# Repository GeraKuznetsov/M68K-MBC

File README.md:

A M68k Multi-Board Computer design. The design basics is as follows:
1) A backplane PCB contains the majority of the bus, such as the address and data lines.
2) Cards slot into the backplane. Cards other then the CPU card should have bus buffers to lower the bus load. (I might give the CPU card buffers too).
3) The 68k's 16MB memory map is split into 16 1MB regions. This is because the two memory chips used, the sst39f040 flash and AS6C4008 ram are both 0.5MB. (So when you put two of them together to get 16 bits, you end up with 1MB per bank).
4) Address decoding is done by a pair of decoders on the CPU card. The CS lines from a header on the side of the CPU card to headers on the sides of the other cards, ideally with a twisted ground for each CS line. In the future these lines could be moved into the backplane. 
5) If the card is less then 10x10 cm, I make it 4-layer. 4-layer boards bigger then 10x10cm are too expensive. 
6) the connectors are DIN41612
7) Line the 16 CS lines, the 7 interrupt lines are also jumpers you plug into the side of the board. There are also 8 interrupt enable jumpers that need to go from the IO card to the CPU card if you want to use one of the parallel output ports as an interrupt enable status port. 

IO and CPU cards are currently completely untested, and the memory card is missing a chip to enable the card's data transmitters. 

/Schematic/:
The actual MBC schematics
Note: LS components are sometimes used when the library has no corresponding HC part. All parts are meant to be HC, with the exception of LVC in 5v->3v translation (output to SD card) and HCT in 3v->5v translation (input from SD card). You can use ACT (or AC if you are feeling brave) but at <16Mhz there should not be a need for fast ACT/AC buffers/gluelogic, especially due to the 68k's slow bus cycles (in comparison to say a 6502 or a z80).

Schematics/BP - design for the backplane (TESTED)
Schematics/CPU - design for CPU card. (NOT TESTED)
Schematics/IO - design for IO card with SD card, PIO, PS2, RTC. (NOT TESTED)
Schematics/MEMv2 - second version of the memory card, doesn't even have the layout done. (NOT FINISHED)
Schematics/MEMv1 - first version of the memory card, missing 74HC20 and gate to enable the card bus buffers (TESTED)
Schematics/Footpp - various footprints
Schematics/Lib - various symbols

/Code/
WIP code, just testing stuff, will eventually be OS

/sst39f040_inBB/:
Allows you to connect an arduino mega to the backplane and program the flash chips on the memory card in-circuit. 
TODO: document this better
sst39f040_inBB/avr - the arduino mega code
sst39f040_inBB/send.py - script file to send the data, requires serial lib

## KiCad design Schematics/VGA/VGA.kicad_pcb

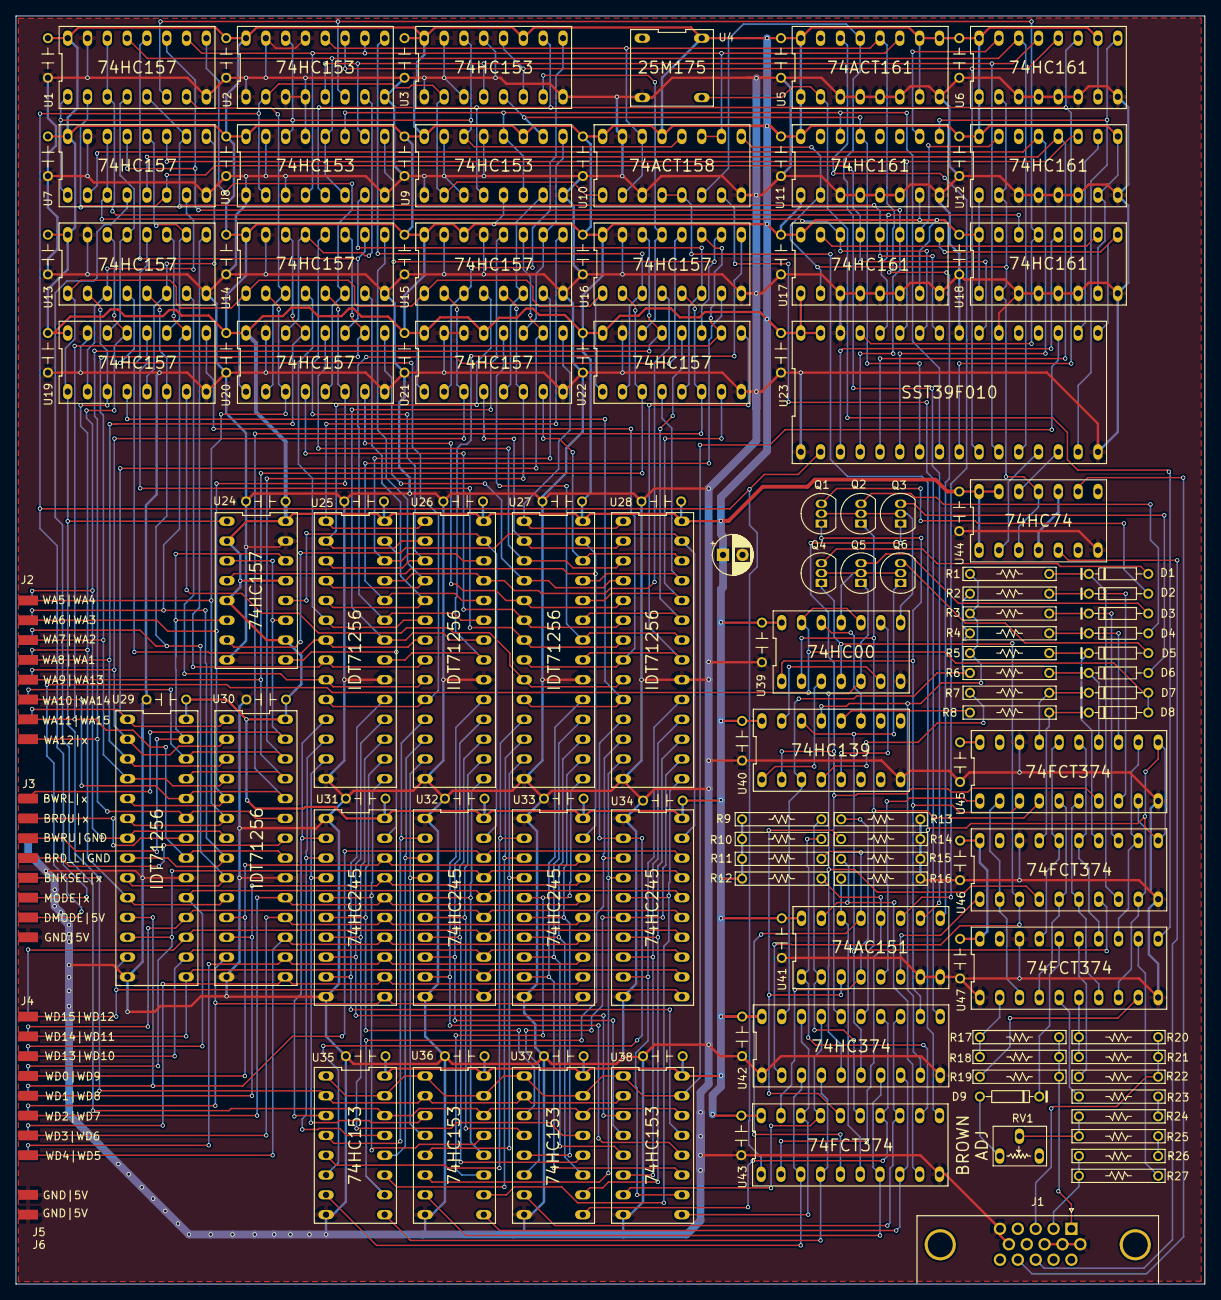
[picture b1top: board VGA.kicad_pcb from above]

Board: 2 copper layers, 152.4 x 162.6 mm, 143 parts (0 on the bottom side), 229 nets.

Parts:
C1, C2, C3, C4, C5, C6, C7, C8, C9, C10, C11, C12, C13, C14, C15, C16, C17, C18, C19, C20, C21, C22, C23, C24, C25, C26, C27, C28, C29, C30, C31, C32, C33, C34, C35, C36, C37, C38, C39, C40, C41, C42, C43, C44, C45, C46: 100nF; DIP-2_200_ELL
C48: C_Polarized_Small; CP_Radial_D5.0mm_P2.50mm
D1, D2, D3, D4, D5, D6, D7, D8, D9: D
J1: DB15_Female; DSUB-15-HD_Female_Horizontal_P2.29x1.98mm_EdgePinOffset3.03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
J2, J4: 2x08; 2x08 finger
J3: 02x08; 2x08 finger
J5, J6: Conn_02x01; 2x01 finger
Q1, Q2, Q3, Q4, Q5, Q6: Q_PNP; TO-92_Inline
R1, R2, R3, R4, R5, R6, R7, R8, R9, R10, R11, R12, R13, R14, R15, R16: R; res
R17, R18, R20, R21: 1K4; res
R19, R22, R27: 1K3; res
R23, R25: 130; res
R24, R26: 220; res
RV1: R_Pot; POT
U1, U7, U13, U14, U15, U16, U19, U20, U21, U22, U24: 74HC157; DIP-16
U2, U3, U8, U9, U35, U36, U37, U38: HC153; DIP-16
U4: mxo45hs-8; DIP-2x2osci
U5: 74ACT161; DIP-16
U6, U11, U12, U17, U18: 74HC161; DIP-16
U10: 74ACT158; DIP-16
U23: SST39F040; DIP-32_600_ELL
U25, U26, U27, U28, U29, U30: 71256(32Kx8); DIP-28
U31, U32, U33, U34: 74HC245; DIP-20
U39: 74HC00; DIP-14
U40: 74LS139; DIP-16
U41: 74F151; DIP-16
U42: 74HC374; DIP-20
U43, U45, U46, U47: 74FCT374; DIP-20
U44: 74HC74; DIP-14

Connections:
+5V: C1.1, C2.1, C3.1, C4.1, C5.1, C6.1, C7.1, C8.1, C9.1, C10.1, C11.1, C12.1, C13.1, C14.1, C15.1, C16.1, C17.1, C18.1, C19.1, C20.1, C21.1, C22.1, C23.1, C24.1, C25.1, C26.1, C27.1, C28.1, C29.1, C30.1, C31.1, C32.1, C33.1, C34.1, C35.1, C36.1, C37.1, C38.1, C39.1, C40.1, C41.1, C42.1, C43.1, C44.1, C45.1, C46.1, C48.1, J3.15, J3.16, J5.2, J6.2, R9.2, R10.2, R11.2, R12.2, U1.16 (VCC), U2.16 (VCC), U3.11 (1B), U3.16 (VCC), U4.8 (Vcc), U5.1 (~MR), U5.7 (CEP), U5.9 (~PE), U5.10 (CET), U5.16 (VCC), U6.1 (~MR), U6.7 (CEP), U6.10 (CET), U6.16 (VCC), U7.16 (VCC), U8.16 (VCC), U9.5 (1A), U9.11 (1B), U9.16 (VCC), U10.13 (I1c), U10.16 (VCC), U11.1 (~MR), U11.7 (CEP), U11.16 (VCC), U12.1 (~MR), U12.7 (CEP), U12.9 (~PE), U12.16 (VCC), U13.16 (VCC), U14.16 (VCC), U15.14 (0D), U15.16 (VCC), U16.16 (VCC), U17.1 (~MR), U17.7 (CEP), U17.16 (VCC), U18.1 (~MR), U18.7 (CEP), U18.16 (VCC), U19.16 (VCC), U20.16 (VCC), U21.13 (1D), U21.16 (VCC), U22.16 (VCC), U23.31 (~WE), U23.32 (Vcc), U24.2 (0A), U24.5 (0B), U24.10 (1C), U24.13 (1D), U24.16 (VCC), U25.28 (Vcc), U26.28 (Vcc), U27.28 (Vcc), U28.28 (Vcc), U29.28 (Vcc), U30.28 (Vcc), U31.20 (VCC), U32.20 (VCC), U33.20 (VCC), U34.20 (VCC), U35.16 (VCC), U36.16 (VCC), U37.16 (VCC), U38.16 (VCC), U39.14 (VCC), U40.16 (VCC)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
/FETCH_ADD_MUX/COL/~MASK: U1.1 (S), U2.14 (S0), U3.14 (S0), U7.1 (S), U8.14 (S0), U9.14 (S0), U10.12 (Zc)
/FETCH_ADD_MUX/MODE: J3.6, U2.2 (S1), U3.2 (S1), U8.2 (S1), U9.2 (S1), U10.1 (S), U23.2 (A16), U43.1 (OE)
/FETCH_ADD_MUX/RA0: U7.4 (ZA), U35.14 (S0), U36.14 (S0), U37.14 (S0), U38.14 (S0)
/FETCH_ADD_MUX/RA1: U7.7 (ZB), U13.3 (1A), U19.2 (0A)
/FETCH_ADD_MUX/RA2: U7.9 (ZC), U13.6 (1B), U19.5 (0B)
/FETCH_ADD_MUX/RA3: U7.12 (ZD), U13.10 (1C), U19.11 (0C)
/FETCH_ADD_MUX/RA4: U1.4 (ZA), U13.13 (1D), U19.14 (0D)
/FETCH_ADD_MUX/RA5: U1.7 (ZB), U14.3 (1A), U20.2 (0A)
/FETCH_ADD_MUX/RA6: U1.9 (ZC), U14.6 (1B), U20.5 (0B)
/FETCH_ADD_MUX/RA7: U1.12 (ZD), U14.10 (1C), U20.11 (0C)
/FETCH_ADD_MUX/RA8: U2.7 (A), U14.13 (1D), U20.14 (0D)
/FETCH_ADD_MUX/RA9: U2.9 (B), U16.3 (1A), U22.2 (0A)
/FETCH_ADD_MUX/RA10: U8.7 (A), U16.6 (1B), U22.5 (0B)
/FETCH_ADD_MUX/RA11: U8.9 (B), U16.10 (1C), U22.11 (0C)
/FETCH_ADD_MUX/RA12: U3.7 (A), U16.13 (1D), U22.14 (0D)
/FETCH_ADD_MUX/RA13: U3.9 (B), U15.3 (1A), U21.2 (0A)
/FETCH_ADD_MUX/RA14: U9.7 (A), U15.6 (1B), U21.5 (0B)
/FETCH_ADD_MUX/RA15: U9.9 (B), U15.10 (1C), U21.11 (0C)
/FETCH_ADD_MUX/X0: U5.14 (Q0), U41.11 (A)
/FETCH_ADD_MUX/X1: U5.13 (Q1), U10.6 (I1b), U41.10 (B)
/FETCH_ADD_MUX/X2: U2.12 (2B), U5.12 (Q2), U10.2 (I0a), U10.14 (I0c), U41.9 (C)
/FETCH_ADD_MUX/X3: U1.10 (1C), U2.10 (0B), U5.11 (Q3), U8.4 (2A), U10.10 (I1d), U10.11 (I0d)
/FETCH_ADD_MUX/X4: U1.13 (1D), U6.14 (Q0), U8.6 (0A), U8.12 (2B), U23.12 (A0)
/FETCH_ADD_MUX/X5: U2.5 (1A), U3.4 (2A), U6.13 (Q1), U8.10 (0B), U23.11 (A1)
/FETCH_ADD_MUX/X6: U2.11 (1B), U3.6 (0A), U3.12 (2B), U6.12 (Q2), U23.10 (A2)
/FETCH_ADD_MUX/X7: U3.10 (0B), U6.11 (Q3), U8.5 (1A), U9.4 (2A), U23.9 (A3)
/FETCH_ADD_MUX/X8: U8.11 (1B), U9.6 (0A), U9.12 (2B), U11.14 (Q0), U23.8 (A4)
/FETCH_ADD_MUX/X9: U3.5 (1A), U9.10 (0B), U11.13 (Q1), U23.7 (A5)
/FETCH_ADD_MUX/Y0: U7.2 (0A), U12.13 (Q1), U23.6 (A6)
/FETCH_ADD_MUX/Y1: U7.5 (0B), U12.12 (Q2), U23.5 (A7)
/FETCH_ADD_MUX/Y2: U7.11 (0C), U12.11 (Q3), U23.27 (A8)
/FETCH_ADD_MUX/Y3: U7.3 (1A), U7.14 (0D), U17.14 (Q0), U23.26 (A9)
/FETCH_ADD_MUX/Y4: U1.2 (0A), U7.6 (1B), U17.13 (Q1), U23.23 (A10)
/FETCH_ADD_MUX/Y5: U1.5 (0B), U7.10 (1C), U17.12 (Q2), U23.25 (A11)
/FETCH_ADD_MUX/Y6: U1.11 (0C), U7.13 (1D), U17.11 (Q3), U23.4 (A12)
/FETCH_ADD_MUX/Y7: U1.3 (1A), U1.14 (0D), U18.14 (Q0), U23.28 (A13)
/FETCH_ADD_MUX/Y8: U1.6 (1B), U2.6 (0A), U18.13 (Q1), U23.29 (A14)
/FETCH_ADD_MUX/Y9: U18.12 (Q2), U23.3 (A15)
/Input/BankSel: J3.5, U13.1 (S), U14.1 (S), U15.1 (S), U16.1 (S), U19.1 (S), U20.1 (S), U21.1 (S), U22.1 (S), U24.1 (S), U35.2 (S1), U36.2 (S1), U37.2 (S1), U38.2 (S1)
/Input/DAC_MODE: D7.2 (A), D8.2 (A), J3.7, U39.10, U39.13
/Input/WA1: J2.13, U13.2 (0A), U19.3 (1A), U29.10 (A0), U30.10 (A0)
/Input/WA2: J2.14, U13.5 (0B), U19.6 (1B), U29.9 (A1), U30.9 (A1)
/Input/WA3: J2.15, U13.11 (0C), U19.10 (1C), U29.8 (A2), U30.8 (A2)
/Input/WA4: J2.16, U13.14 (0D), U19.13 (1D), U29.7 (A3), U30.7 (A3)
/Input/WA5: J2.8, U14.2 (0A), U20.3 (1A), U29.6 (A4), U30.6 (A4)
/Input/WA6: J2.7, U14.5 (0B), U20.6 (1B), U29.5 (A5), U30.5 (A5)
/Input/WA7: J2.6, U14.11 (0C), U20.10 (1C), U29.4 (A6), U30.4 (A6)
/Input/WA8: J2.5, U14.14 (0D), U20.13 (1D), U29.3 (A7), U30.3 (A7)
/Input/WA9: J2.4, U16.2 (0A), U22.3 (1A), U29.25 (A8), U30.25 (A8)
/Input/WA10: J2.3, U16.5 (0B), U22.6 (1B), U29.24 (A9), U30.24 (A9)
/Input/WA11: J2.2, U16.11 (0C), U22.10 (1C), U29.21 (A10), U30.21 (A10)
/Input/WA12: J2.1, U16.14 (0D), U22.13 (1D), U29.23 (A11), U30.23 (A11)
/Input/WA13: J2.12, U15.2 (0A), U21.3 (1A), U29.2 (A12), U30.2 (A12)
/Input/WA14: J2.11, U15.5 (0B), U21.6 (1B), U29.26 (A13), U30.26 (A13)
/Input/WA15: J2.10, U15.11 (0C), U21.10 (1C), U29.1 (A14), U30.1 (A14)
/Input/WD0: J4.5, U30.11 (D0), U31.18 (B0), U33.18 (B0)
/Input/WD1: J4.4, U30.12 (D1), U31.17 (B1), U33.17 (B1)
/Input/WD2: J4.3, U30.19 (D7), U31.16 (B2), U33.16 (B2)
/Input/WD3: J4.2, U30.18 (D6), U31.15 (B3), U33.15 (B3)
/Input/WD4: J4.1, U30.17 (D5), U31.14 (B4), U33.14 (B4)
/Input/WD5: J4.9, U30.16 (D4), U31.13 (B5), U33.13 (B5)
/Input/WD6: J4.10, U30.15 (D3), U31.12 (B6), U33.12 (B6)
/Input/WD7: J4.11, U30.13 (D2), U31.11 (B7), U33.11 (B7)
/Input/WD8: J4.12, U29.11 (D0), U32.18 (B0), U34.18 (B0)
/Input/WD9: J4.13, U29.12 (D1), U32.17 (B1), U34.17 (B1)
/Input/WD10: J4.14, U29.19 (D7), U32.16 (B2), U34.16 (B2)
/Input/WD11: J4.15, U29.18 (D6), U32.15 (B3), U34.15 (B3)
/Input/WD12: J4.16, U29.17 (D5), U32.14 (B4), U34.14 (B4)
/Input/WD13: J4.6, U29.16 (D4), U32.13 (B5), U34.13 (B5)
/Input/WD14: J4.7, U29.15 (D3), U32.12 (B6), U34.12 (B6)
/Input/WD15: J4.8, U29.13 (D2), U32.11 (B7), U34.11 (B7)
/Input/~BRD_L: J3.4, U30.22 (~OE)
/Input/~BRD_U: J3.2, U29.22 (~OE)
/Input/~BWR_L: J3.1, U24.3 (1A), U24.11 (0C), U30.27 (~WE)
/Input/~BWR_U: J3.3, U24.6 (1B), U24.14 (0D), U29.27 (~WE)
/Output/B0: Q3.1 (E), U40.2 (A0), U42.16 (O6), U45.7 (D2)
/Output/B1: Q6.1 (E), U40.14 (A0), U42.6 (O2), U46.7 (D2)
/Output/BLUE: J1.3, R20.2, R21.2, R22.2
/Output/BROWN0: D7.1 (K), R7.1, U45.17 (D6)
/Output/BROWN1: D8.1 (K), R8.1, U46.17 (D6)
/Output/G0: Q2.1 (E), U39.2, U42.15 (O5), U45.4 (D1)
/Output/G1: Q5.1 (E), U39.5, U42.5 (O1), U46.4 (D1)
/Output/GREEN: J1.2, R26.1, R27.2
/Output/I0: R2.2, R4.2, R6.2, U40.3 (A1), U42.19 (O7)
/Output/I1: R1.2, R3.2, R5.2, U40.13 (A1), U42.9 (O3)
/Output/IB0: D6.1 (K), R6.1, U45.14 (D5)
/Output/IB1: D5.1 (K), R5.1, U46.14 (D5)
/Output/IG0: D4.1 (K), R4.1, U45.13 (D4)
/Output/IG1: D3.1 (K), R3.1, U46.13 (D4)
/Output/IR0: D2.1 (K), R2.1, U45.8 (D3)
/Output/IR1: D1.1 (K), R1.1, U46.8 (D3)
/Output/LATCH_COLOR: U10.7 (Zb), U42.11 (Cp)
/Output/LATCH_MASK: U10.4 (Za), U10.5 (I0b), U43.11 (Cp), U45.11 (Cp), U46.11 (Cp)
/Output/LATCH_PIX: U4.5 (Out), U5.2 (CP), U47.11 (Cp)
/Output/R0: Q1.1 (E), U39.1, U42.12 (O4), U45.3 (D0)
/Output/R1: Q4.1 (E), U39.4, U42.2 (O0), U46.3 (D0)
/Output/RD0: U35.7 (A), U42.3 (D0), U43.3 (D0)
/Output/RD1: U35.9 (B), U42.4 (D1), U43.4 (D1)
/Output/RD2: U36.7 (A), U42.7 (D2), U43.7 (D2)
/Output/RD3: U36.9 (B), U42.8 (D3), U43.8 (D3)
/Output/RD4: U37.7 (A), U42.13 (D4), U43.13 (D4)
/Output/RD5: U37.9 (B), U42.14 (D5), U43.14 (D5)
/Output/RD6: U38.7 (A), U42.17 (D6), U43.17 (D6)
/Output/RD7: U38.9 (B), U42.18 (D7), U43.18 (D7)
/Output/RED: J1.1, R17.2, R18.2, R19.2
/Output/~HSYNC: J1.13, U44.5 (Q)
/Output/~VSYNC: J1.14, U44.9 (Q)
/SEQ/YINC: U12.10 (CET), U23.18 (D4)
/SEQ/~VIS: U23.19 (D5), U35.1 (~EA), U35.15 (~EB), U36.1 (~EA), U36.15 (~EB), U37.1 (~EA), U37.15 (~EB), U38.1 (~EA), U38.15 (~EB)
/SEQ/~XRES: U6.9 (~PE), U11.9 (~PE), U23.15 (D2)
/SEQ/~YRES: U17.9 (~PE), U18.9 (~PE), U23.17 (D3)
/VRAM/B0A1: U19.4 (ZA), U27.10 (A0), U28.10 (A0)
/VRAM/B0A2: U19.7 (ZB), U27.9 (A1), U28.9 (A1)
/VRAM/B0A3: U19.9 (ZC), U27.8 (A2), U28.8 (A2)
/VRAM/B0A4: U19.12 (ZD), U27.7 (A3), U28.7 (A3)
/VRAM/B0A5: U20.4 (ZA), U27.6 (A4), U28.6 (A4)
/VRAM/B0A6: U20.7 (ZB), U27.5 (A5), U28.5 (A5)
/VRAM/B0A7: U20.9 (ZC), U27.4 (A6), U28.4 (A6)
/VRAM/B0A8: U20.12 (ZD), U27.3 (A7), U28.3 (A7)
/VRAM/B0A9: U22.4 (ZA), U27.25 (A8), U28.25 (A8)
/VRAM/B0A10: U22.7 (ZB), U27.24 (A9), U28.24 (A9)
/VRAM/B0A11: U22.9 (ZC), U27.21 (A10), U28.21 (A10)
/VRAM/B0A12: U22.12 (ZD), U27.23 (A11), U28.23 (A11)
/VRAM/B0A13: U21.4 (ZA), U27.2 (A12), U28.2 (A12)
/VRAM/B0A14: U21.7 (ZB), U27.26 (A13), U28.26 (A13)
/VRAM/B0A15: U21.9 (ZC), U27.1 (A14), U28.1 (A14)
/VRAM/B0D0: U27.11 (D0), U33.2 (A0), U35.5 (1A)
/VRAM/B0D1: U27.12 (D1), U33.3 (A1), U35.11 (1B)
/VRAM/B0D2: U27.13 (D2), U33.4 (A2), U36.5 (1A)
/VRAM/B0D3: U27.15 (D3), U33.5 (A3), U36.11 (1B)
/VRAM/B0D4: U27.16 (D4), U33.6 (A4), U37.5 (1A)
/VRAM/B0D5: U27.17 (D5), U33.7 (A5), U37.11 (1B)
/VRAM/B0D6: U27.18 (D6), U33.8 (A6), U38.5 (1A)
/VRAM/B0D7: U27.19 (D7), U33.9 (A7), U38.11 (1B)
/VRAM/B0D8: U28.11 (D0), U34.2 (A0), U35.6 (0A)
/VRAM/B0D9: U28.12 (D1), U34.3 (A1), U35.10 (0B)
/VRAM/B0D10: U28.13 (D2), U34.4 (A2), U36.6 (0A)
/VRAM/B0D11: U28.15 (D3), U34.5 (A3), U36.10 (0B)
/VRAM/B0D12: U28.16 (D4), U34.6 (A4), U37.6 (0A)
/VRAM/B0D13: U28.17 (D5), U34.7 (A5), U37.10 (0B)
/VRAM/B0D14: U28.18 (D6), U34.8 (A6), U38.6 (0A)
/VRAM/B0D15: U28.19 (D7), U34.9 (A7), U38.10 (0B)
/VRAM/B1A1: U13.4 (ZA), U25.10 (A0), U26.10 (A0)
/VRAM/B1A2: U13.7 (ZB), U25.9 (A1), U26.9 (A1)
/VRAM/B1A3: U13.9 (ZC), U25.8 (A2), U26.8 (A2)
/VRAM/B1A4: U13.12 (ZD), U25.7 (A3), U26.7 (A3)
/VRAM/B1A5: U14.4 (ZA), U25.6 (A4), U26.6 (A4)
/VRAM/B1A6: U14.7 (ZB), U25.5 (A5), U26.5 (A5)
/VRAM/B1A7: U14.9 (ZC), U25.4 (A6), U26.4 (A6)
/VRAM/B1A8: U14.12 (ZD), U25.3 (A7), U26.3 (A7)
/VRAM/B1A9: U16.4 (ZA), U25.25 (A8), U26.25 (A8)
/VRAM/B1A10: U16.7 (ZB), U25.24 (A9), U26.24 (A9)
/VRAM/B1A11: U16.9 (ZC), U25.21 (A10), U26.21 (A10)
/VRAM/B1A12: U16.12 (ZD), U25.23 (A11), U26.23 (A11)
/VRAM/B1A13: U15.4 (ZA), U25.2 (A12), U26.2 (A12)
/VRAM/B1A14: U15.7 (ZB), U25.26 (A13), U26.26 (A13)
/VRAM/B1A15: U15.9 (ZC), U25.1 (A14), U26.1 (A14)
/VRAM/B1D0: U25.11 (D0), U31.2 (A0), U35.3 (3A)
/VRAM/B1D1: U25.12 (D1), U31.3 (A1), U35.13 (3B)
/VRAM/B1D2: U25.13 (D2), U31.4 (A2), U36.3 (3A)
/VRAM/B1D3: U25.15 (D3), U31.5 (A3), U36.13 (3B)
/VRAM/B1D4: U25.16 (D4), U31.6 (A4), U37.3 (3A)
/VRAM/B1D5: U25.17 (D5), U31.7 (A5), U37.13 (3B)
/VRAM/B1D6: U25.18 (D6), U31.8 (A6), U38.3 (3A)
/VRAM/B1D7: U25.19 (D7), U31.9 (A7), U38.13 (3B)
/VRAM/B1D8: U26.11 (D0), U32.2 (A0), U35.4 (2A)
/VRAM/B1D9: U26.12 (D1), U32.3 (A1), U35.12 (2B)
/VRAM/B1D10: U26.13 (D2), U32.4 (A2), U36.4 (2A)
/VRAM/B1D11: U26.15 (D3), U32.5 (A3), U36.12 (2B)
/VRAM/B1D12: U26.16 (D4), U32.6 (A4), U37.4 (2A)
/VRAM/B1D13: U26.17 (D5), U32.7 (A5), U37.12 (2B)
/VRAM/B1D14: U26.18 (D6), U32.8 (A6), U38.4 (2A)
/VRAM/B1D15: U26.19 (D7), U32.9 (A7), U38.12 (2B)
/VRAM/~B0RD: U21.12 (ZD), U27.22 (~OE), U28.22 (~OE)
/VRAM/~B0WRH: U24.7 (ZB), U28.27 (~WE), U34.19 (CE)
/VRAM/~B0WRL: U24.4 (ZA), U27.27 (~WE), U33.19 (CE)
/VRAM/~B1RD: U15.12 (ZD), U25.22 (~OE), U26.22 (~OE)
/VRAM/~B1WRH: U24.12 (ZD), U26.27 (~WE), U32.19 (CE)
/VRAM/~B1WRL: U24.9 (ZC), U25.27 (~WE), U31.19 (CE)
GND: C1.2, C2.2, C3.2, C4.2, C5.2, C6.2, C7.2, C8.2, C9.2, C10.2, C11.2, C12.2, C13.2, C14.2, C15.2, C16.2, C17.2, C18.2, C19.2, C20.2, C21.2, C22.2, C23.2, C24.2, C25.2, C26.2, C27.2, C28.2, C29.2, C30.2, C31.2, C32.2, C33.2, C34.2, C35.2, C36.2, C37.2, C38.2, C39.2, C40.2, C41.2, C42.2, C43.2, C44.2, C45.2, C46.2, C48.2, J1.5, J1.6, J1.7, J1.8, J1.10, J3.8, J3.11, J3.12, J5.1, J6.1, R13.1, R14.1, R15.1, R16.1, U1.8 (GND), U1.15 (E), U2.1 (~EA), U2.3 (3A), U2.4 (2A), U2.8 (GND), U2.13 (3B), U2.15 (~EB), U3.1 (~EA), U3.3 (3A), U3.8 (GND), U3.13 (3B), U3.15 (~EB), U4.4 (Gnd), U5.3 (D0), U5.4 (D1), U5.5 (D2), U5.6 (D3), U5.8 (GND), U6.3 (D0), U6.4 (D1), U6.5 (D2), U6.6 (D3), U6.8 (GND), U7.8 (GND), U7.15 (E), U8.1 (~EA), U8.3 (3A), U8.8 (GND), U8.13 (3B), U8.15 (~EB), U9.1 (~EA), U9.3 (3A), U9.8 (GND), U9.13 (3B), U9.15 (~EB), U10.3 (I1a), U10.8 (GND), U10.15 (E), U11.3 (D0), U11.4 (D1), U11.5 (D2), U11.6 (D3), U11.8 (GND), U12.3 (D0), U12.4 (D1), U12.5 (D2), U12.6 (D3), U12.8 (GND), U13.8 (GND), U13.15 (E), U14.8 (GND), U14.15 (E), U15.8 (GND), U15.13 (1D), U15.15 (E), U16.8 (GND), U16.15 (E), U17.3 (D0), U17.4 (D1), U17.5 (D2)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
unnamed: D1.2 (A), Q4.3 (C)
unnamed: D2.2 (A), Q1.3 (C)
unnamed: D3.2 (A), Q5.3 (C)
unnamed: D4.2 (A), Q2.3 (C)
unnamed: D5.2 (A), Q6.3 (C)
unnamed: D6.2 (A), Q3.3 (C)
unnamed: D9.2 (A), RV1.1
unnamed: D9.1 (K), U47.16 (O6)
unnamed: Q1.2 (B), Q2.2 (B), Q3.2 (B), U39.8
unnamed: Q4.2 (B), Q5.2 (B), Q6.2 (B), U39.11
unnamed: R23.2, R24.2
unnamed: R24.1, R25.1, RV1.2
unnamed: R25.2, R26.2
unnamed: U6.2 (CP), U10.9 (Zd), U11.2 (CP), U12.2 (CP), U17.2 (CP), U18.2 (CP), U44.3 (C), U44.11 (C)
unnamed: U6.15 (TC), U11.10 (CET)
unnamed: U12.15 (TC), U17.10 (CET)
unnamed: U17.15 (TC), U18.10 (CET)
unnamed: U23.13 (D0), U44.2 (D)
unnamed: U23.14 (D1), U44.12 (D)
unnamed: U39.3, U40.1 (E)
unnamed: R7.2, U40.4 (O0)
unnamed: U39.9, U40.5 (O1)
unnamed: U39.6, U40.15 (E)
unnamed: R8.2, U40.12 (O0)
unnamed: U39.12, U40.11 (O1)
unnamed: R13.2, U41.4 (D0), U43.19 (O7)
unnamed: R14.2, U41.3 (D1), U43.16 (O6)
unnamed: R9.1, U41.2 (D2), U43.15 (O5)
unnamed: R10.1, U41.1 (D3), U43.12 (O4)
unnamed: R15.2, U41.15 (D4), U43.9 (O3)
unnamed: R16.2, U41.14 (D5), U43.6 (O2)
unnamed: R11.1, U41.13 (D6), U43.5 (O1)
unnamed: R12.1, U41.12 (D7), U43.2 (O0)
unnamed: U41.5 (O), U45.1 (OE)
unnamed: U41.6 (~O), U46.1 (OE)
unnamed: U45.2 (O0), U46.2 (O0), U47.3 (D0)
unnamed: U45.5 (O1), U46.5 (O1), U47.4 (D1)
unnamed: U45.6 (O2), U46.6 (O2), U47.7 (D2)
unnamed: U45.9 (O3), U46.9 (O3), U47.8 (D3)
unnamed: U45.12 (O4), U46.12 (O4), U47.13 (D4)
unnamed: U45.15 (O5), U46.15 (O5), U47.14 (D5)
unnamed: U45.16 (O6), U46.16 (O6), U47.17 (D6)
unnamed: R17.1, R18.1, U47.2 (O0)
unnamed: R23.1, U47.5 (O1)
unnamed: R20.1, R21.1, U47.6 (O2)
unnamed: R19.1, U47.9 (O3)
unnamed: R27.1, U47.12 (O4)
unnamed: R22.1, U47.15 (O5)

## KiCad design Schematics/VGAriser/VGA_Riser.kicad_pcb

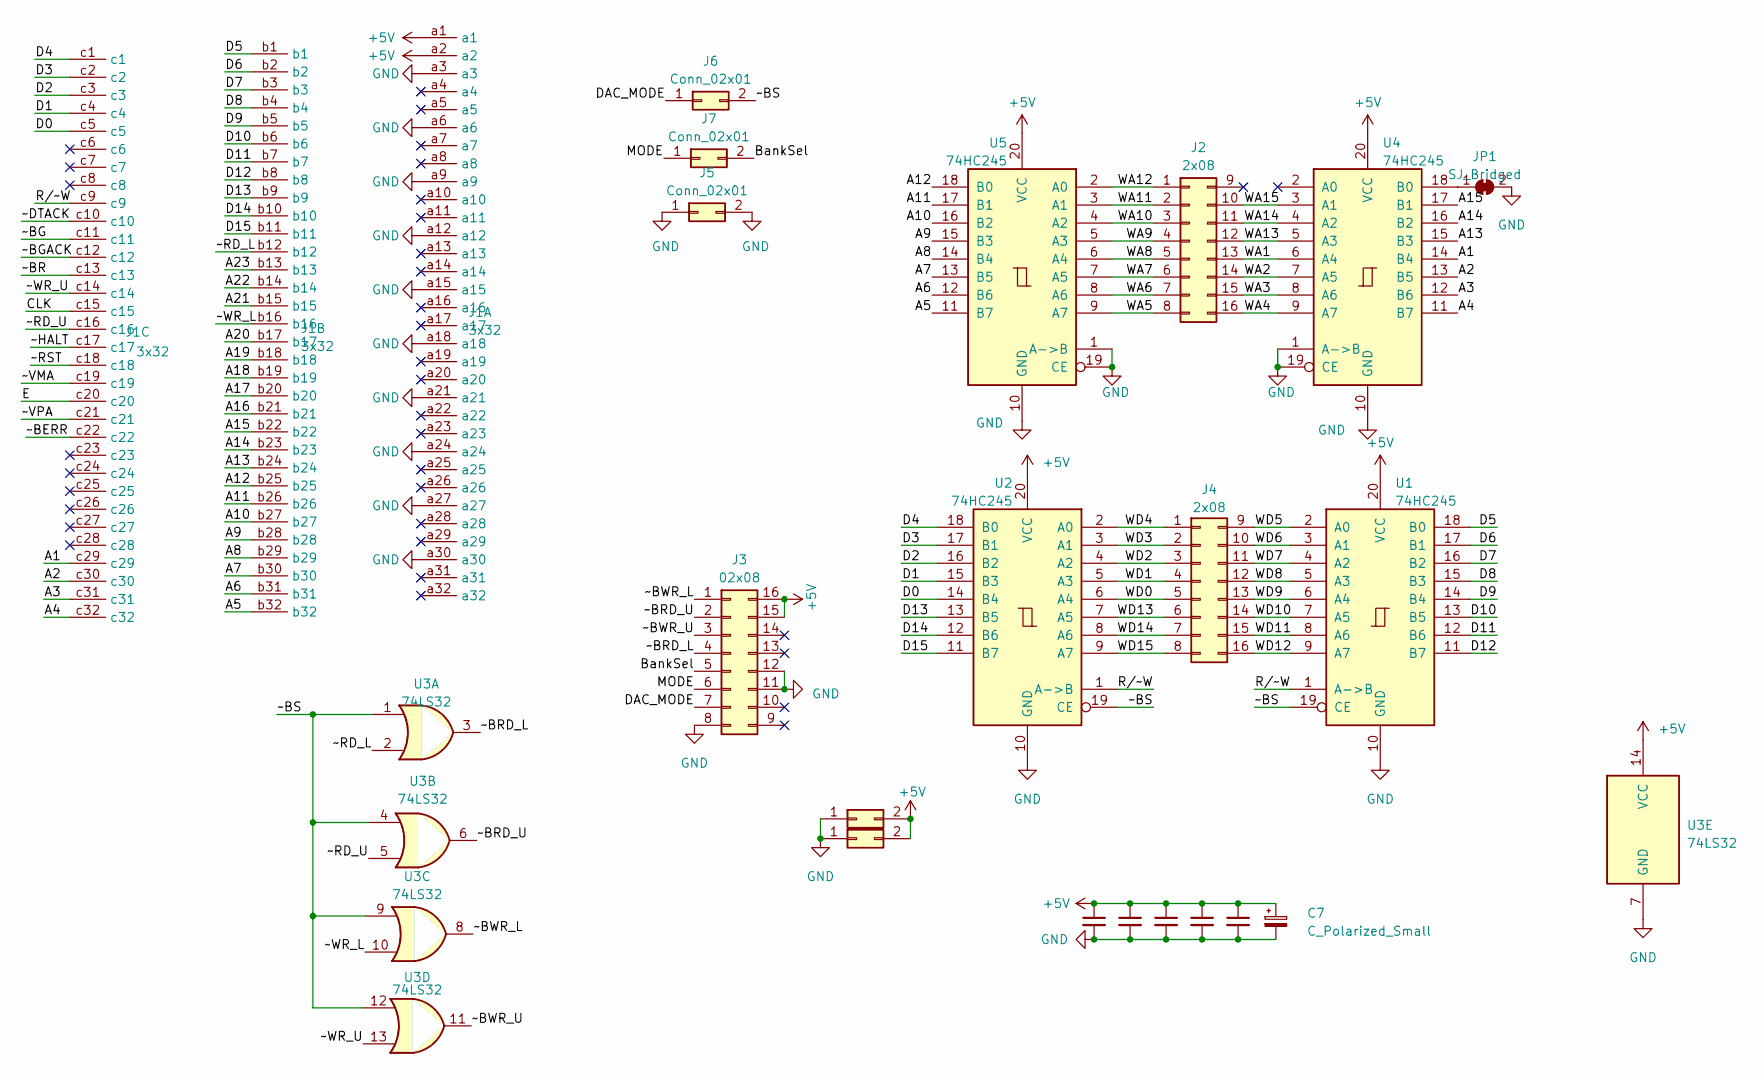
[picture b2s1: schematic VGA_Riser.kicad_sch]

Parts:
C1, C2, C3, C4, C5: 100nF; DIP-2_200_ELL
C7: C_Polarized_Small; CP_Radial_D5.0mm_P2.50mm
J1: 3x32; DIN41612_R_3x32_Male_Horizontal_THT
J2, J4: 2x08; 2x08 finger
J3: 02x08; 2x08 finger
J5, J6, J7: Conn_02x01; 2x01 finger
JP1: SJ_Bridged; SolderJumper-2_P1.3mm_Bridged_Pad1.0x1.5mm
U1, U2, U4, U5: 74HC245; DIP-20
U3: 74LS32; DIP-14

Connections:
/A1: J1.c29, U4.14 (B4)
/A2: J1.c30, U4.13 (B5)
/A3: J1.c31, U4.12 (B6)
/A4: J1.c32, U4.11 (B7)
/A5: J1.b32, U5.11 (B7)
/A6: J1.b31, U5.12 (B6)
/A7: J1.b30, U5.13 (B5)
/A8: J1.b29, U5.14 (B4)
/A9: J1.b28, U5.15 (B3)
/A10: J1.b27, U5.16 (B2)
/A11: J1.b26, U5.17 (B1)
/A12: J1.b25, U5.18 (B0)
/A13: J1.b24, U4.15 (B3)
/A14: J1.b23, U4.16 (B2)
/A15: J1.b22, U4.17 (B1)
/A16: J1.b21
/A17: J1.b20
/A18: J1.b19
/A19: J1.b18
/A20: J1.b17
/A21: J1.b15
/A22: J1.b14
/A23: J1.b13
/BankSel: J3.5, J7.2
/CLK: J1.c15
/D0: J1.c5, U2.14 (B4)
/D1: J1.c4, U2.15 (B3)
/D2: J1.c3, U2.16 (B2)
/D3: J1.c2, U2.17 (B1)
/D4: J1.c1, U2.18 (B0)
/D5: J1.b1, U1.18 (B0)
/D6: J1.b2, U1.17 (B1)
/D7: J1.b3, U1.16 (B2)
/D8: J1.b4, U1.15 (B3)
/D9: J1.b5, U1.14 (B4)
/D10: J1.b6, U1.13 (B5)
/D11: J1.b7, U1.12 (B6)
/D12: J1.b8, U1.11 (B7)
/D13: J1.b9, U2.13 (B5)
/D14: J1.b10, U2.12 (B6)
/D15: J1.b11, U2.11 (B7)
/E: J1.c20
/MODE: J3.6, J7.1
/R/~W: J1.c9, U1.1 (A->B), U2.1 (A->B)
/WA1: J2.13, U4.6 (A4)
/WA2: J2.14, U4.7 (A5)
/WA3: J2.15, U4.8 (A6)
/WA4: J2.16, U4.9 (A7)
/WA5: J2.8, U5.9 (A7)
/WA6: J2.7, U5.8 (A6)
/WA7: J2.6, U5.7 (A5)
/WA8: J2.5, U5.6 (A4)
/WA9: J2.4, U5.5 (A3)
/WA10: J2.3, U5.4 (A2)
/WA11: J2.2, U5.3 (A1)
/WA12: J2.1, U5.2 (A0)
/WA13: J2.12, U4.5 (A3)
/WA14: J2.11, U4.4 (A2)
/WA15: J2.10, U4.3 (A1)
/WD0: J4.5, U2.6 (A4)
/WD1: J4.4, U2.5 (A3)
/WD2: J4.3, U2.4 (A2)
/WD3: J4.2, U2.3 (A1)
/WD4: J4.1, U2.2 (A0)
/WD5: J4.9, U1.2 (A0)
/WD6: J4.10, U1.3 (A1)
/WD7: J4.11, U1.4 (A2)
/WD8: J4.12, U1.5 (A3)
/WD9: J4.13, U1.6 (A4)
/WD10: J4.14, U1.7 (A5)
/WD11: J4.15, U1.8 (A6)
/WD12: J4.16, U1.9 (A7)
/WD13: J4.6, U2.7 (A5)
/WD14: J4.7, U2.8 (A6)
/WD15: J4.8, U2.9 (A7)
/~BERR: J1.c22
/~BG: J1.c11
/~BGACK: J1.c12
/~BR: J1.c13
/~BRD_L: J3.4, U3.3
/~BRD_U: J3.2, U3.6
/~BWR_L: J3.1, U3.8
/~BWR_U: J3.3, U3.11
/~DTACK: J1.c10
/~HALT: J1.c17
/~RD_L: J1.b12, U3.2
/~RD_U: J1.c16, U3.5
/~RST: J1.c18
/~VMA: J1.c19
/~VPA: J1.c21
/~WR_L: J1.b16, U3.10
/~WR_U: J1.c14, U3.13
unnamed: JP1.1 (A), U4.18 (B0)

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
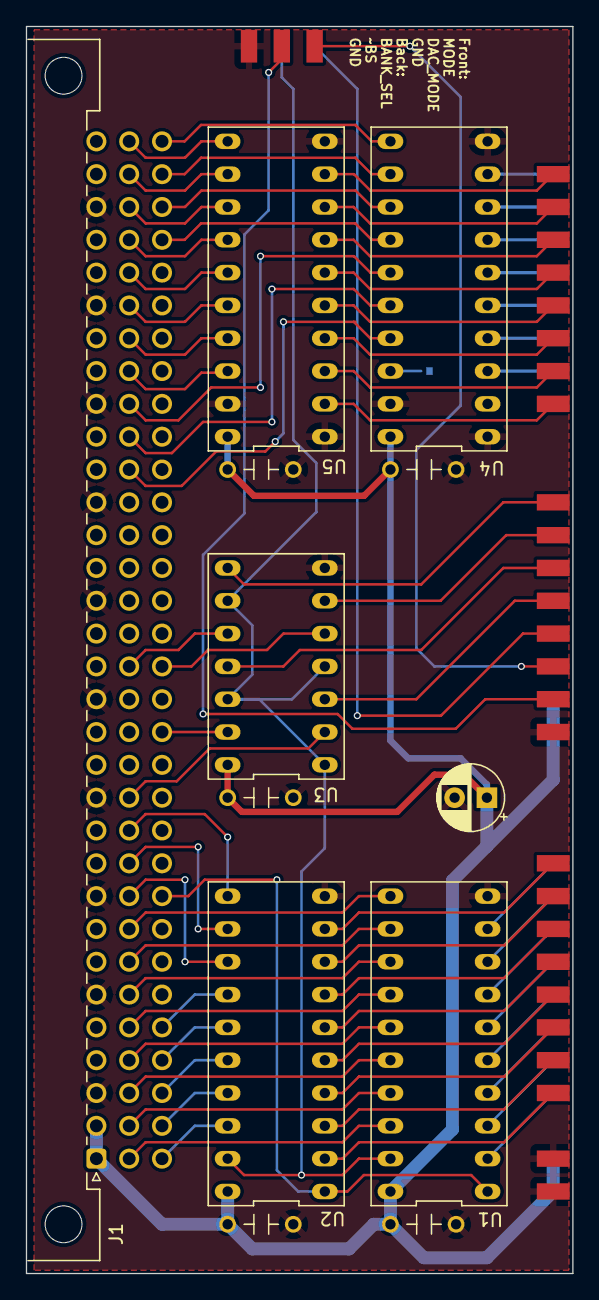
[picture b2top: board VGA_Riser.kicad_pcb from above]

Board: 2 copper layers, 42.3 x 96.5 mm, 21 parts (1 on the bottom side), 78 nets.

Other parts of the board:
J8, J9: Conn_02x01; 2x01 finger

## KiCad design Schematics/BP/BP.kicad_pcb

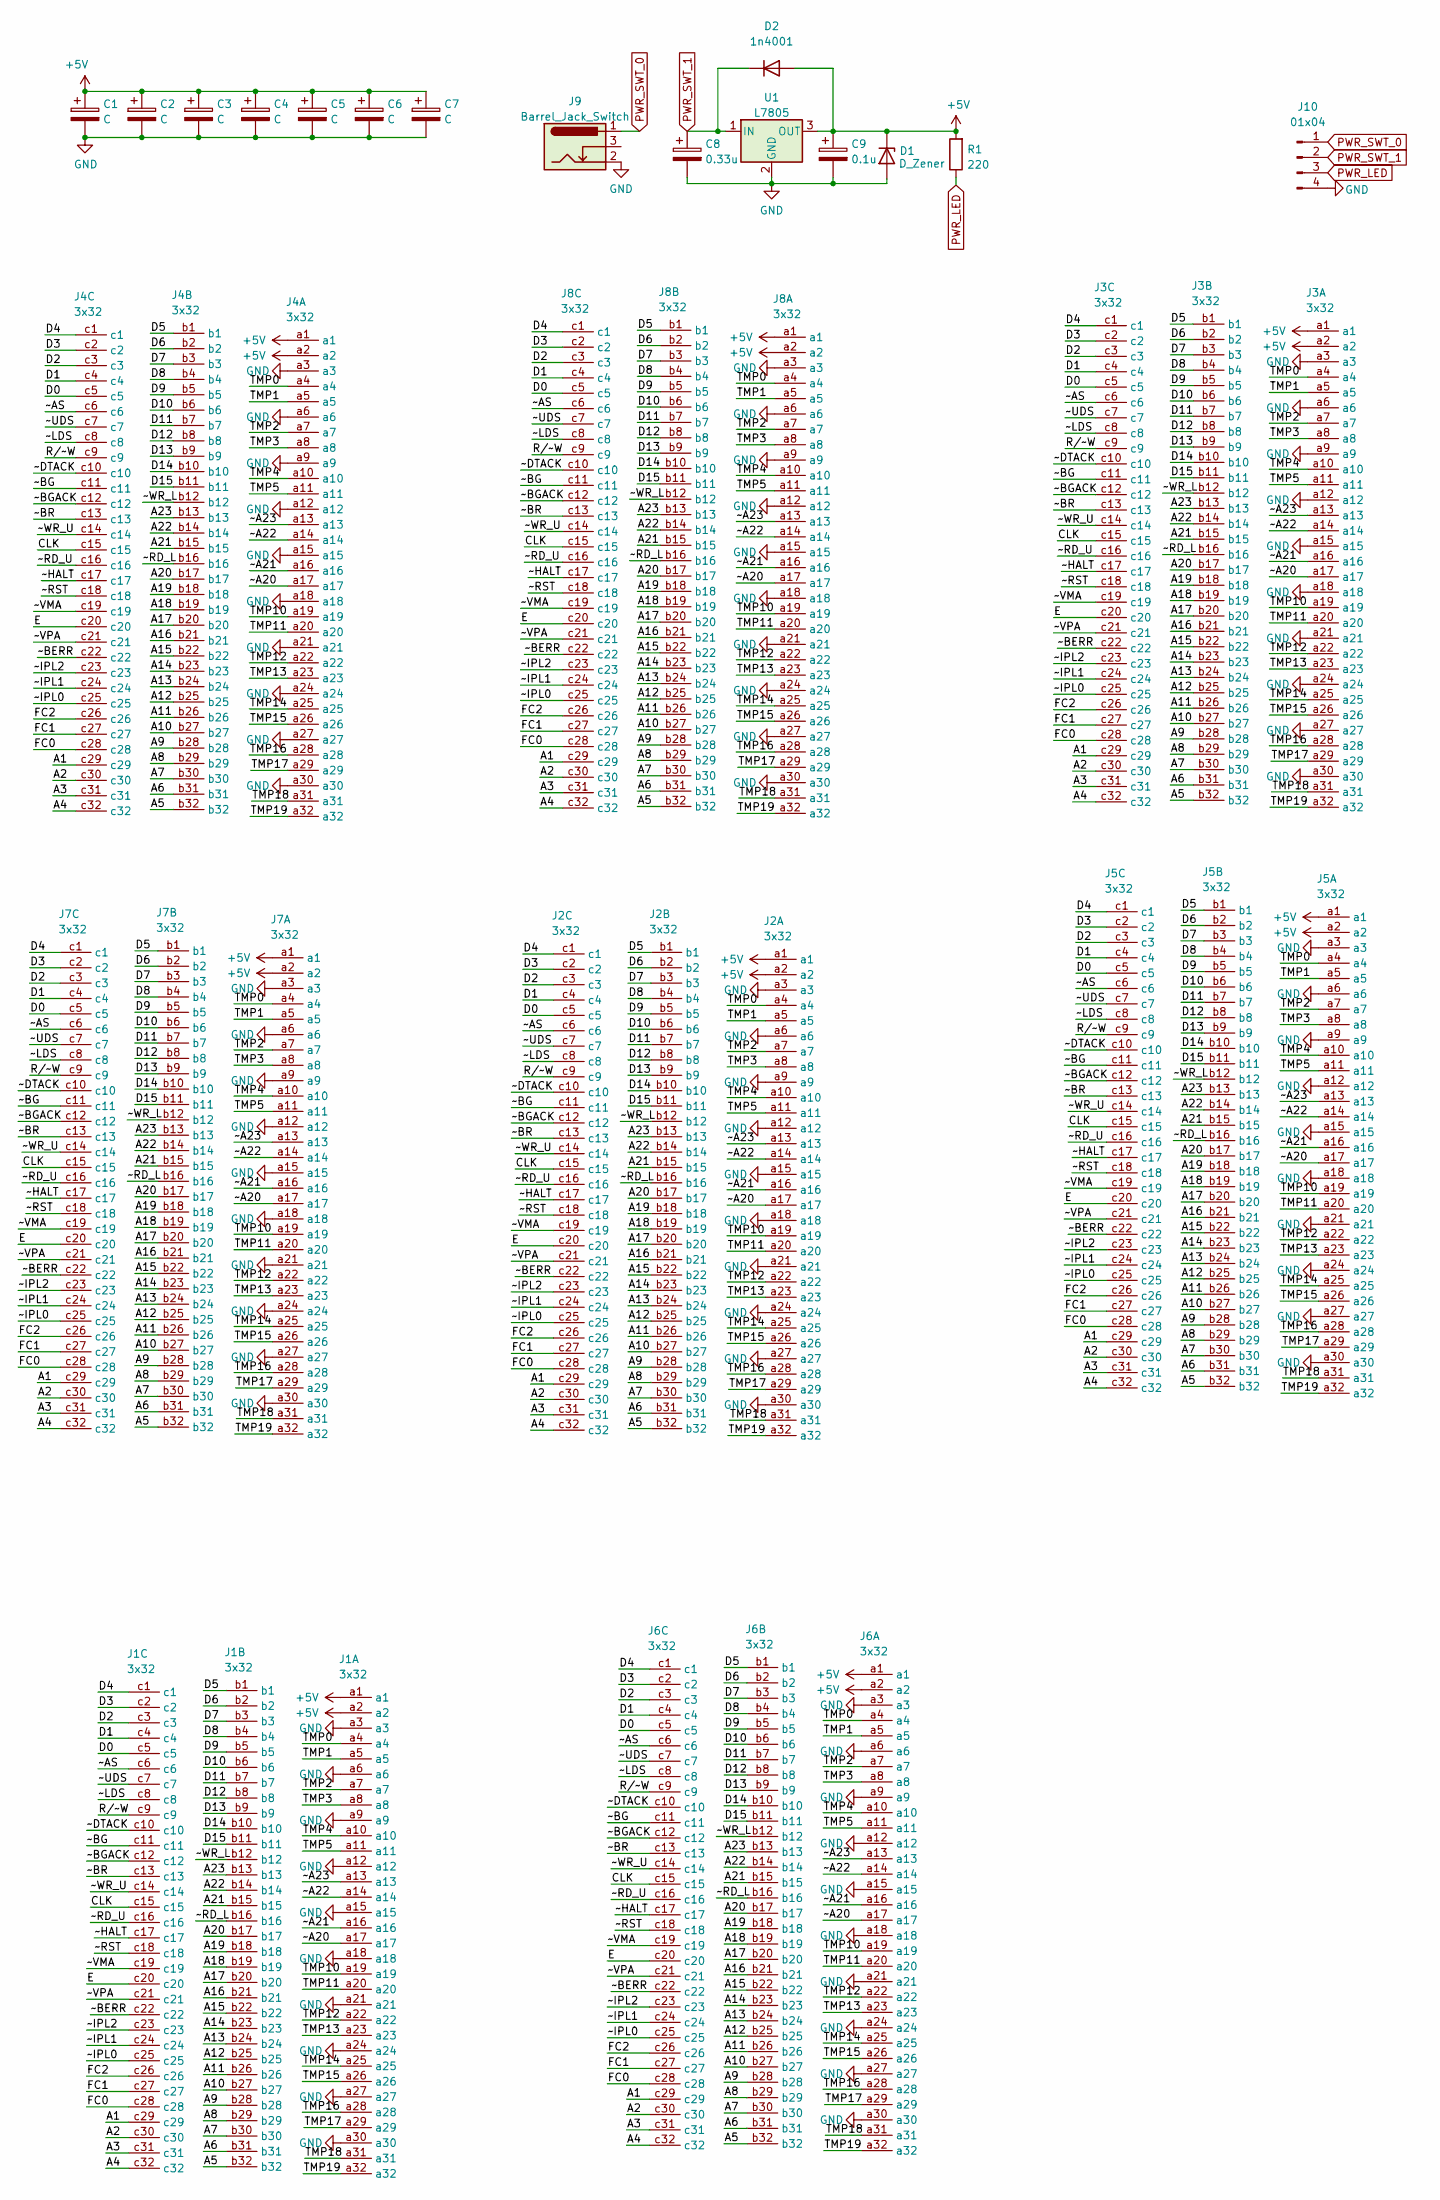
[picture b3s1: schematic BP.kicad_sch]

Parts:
C1, C2, C3, C4, C5, C6, C7: C; CP_Radial_D5.0mm_P2.50mm
C8: 0.33u; CP_Radial_D5.0mm_P2.50mm
C9: 0.1u; CP_Radial_D5.0mm_P2.50mm
D1: D_Zener; D_T-1_P5.08mm_Horizontal
D2: 1n4001; D_T-1_P5.08mm_Horizontal
J1, J2, J3, J4, J5, J6, J7, J8: 3x32; DIN41612_C_3x32_Female_Vertical_THT
J9: Barrel_Jack_Switch; BarrelJack_Horizontal
J10: 01x04
R1: 220; R_Axial_DIN0411_L9.9mm_D3.6mm_P5.08mm_Vertical
U1: L7805; TO-220-3_Horizontal_TabDown

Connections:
+5V: C1.1, C2.1, C3.1, C4.1, C5.1, C6.1, C7.1, C9.1, D1.1 (K), D2.2 (A), J1.a1, J1.a2, J2.a1, J2.a2, J3.a1, J3.a2, J4.a1, J4.a2, J5.a1, J5.a2, J6.a1, J6.a2, J7.a1, J7.a2, J8.a1, J8.a2, R1.2, U1.3 (OUT)
/A1: J1.c29, J2.c29, J3.c29, J4.c29, J5.c29, J6.c29, J7.c29, J8.c29
/A2: J1.c30, J2.c30, J3.c30, J4.c30, J5.c30, J6.c30, J7.c30, J8.c30
/A3: J1.c31, J2.c31, J3.c31, J4.c31, J5.c31, J6.c31, J7.c31, J8.c31
/A4: J1.c32, J2.c32, J3.c32, J4.c32, J5.c32, J6.c32, J7.c32, J8.c32
/A5: J1.b32, J2.b32, J3.b32, J4.b32, J5.b32, J6.b32, J7.b32, J8.b32
/A6: J1.b31, J2.b31, J3.b31, J4.b31, J5.b31, J6.b31, J7.b31, J8.b31
/A7: J1.b30, J2.b30, J3.b30, J4.b30, J5.b30, J6.b30, J7.b30, J8.b30
/A8: J1.b29, J2.b29, J3.b29, J4.b29, J5.b29, J6.b29, J7.b29, J8.b29
/A9: J1.b28, J2.b28, J3.b28, J4.b28, J5.b28, J6.b28, J7.b28, J8.b28
/A10: J1.b27, J2.b27, J3.b27, J4.b27, J5.b27, J6.b27, J7.b27, J8.b27
/A11: J1.b26, J2.b26, J3.b26, J4.b26, J5.b26, J6.b26, J7.b26, J8.b26
/A12: J1.b25, J2.b25, J3.b25, J4.b25, J5.b25, J6.b25, J7.b25, J8.b25
/A13: J1.b24, J2.b24, J3.b24, J4.b24, J5.b24, J6.b24, J7.b24, J8.b24
/A14: J1.b23, J2.b23, J3.b23, J4.b23, J5.b23, J6.b23, J7.b23, J8.b23
/A15: J1.b22, J2.b22, J3.b22, J4.b22, J5.b22, J6.b22, J7.b22, J8.b22
/A16: J1.b21, J2.b21, J3.b21, J4.b21, J5.b21, J6.b21, J7.b21, J8.b21
/A17: J1.b20, J2.b20, J3.b20, J4.b20, J5.b20, J6.b20, J7.b20, J8.b20
/A18: J1.b19, J2.b19, J3.b19, J4.b19, J5.b19, J6.b19, J7.b19, J8.b19
/A19: J1.b18, J2.b18, J3.b18, J4.b18, J5.b18, J6.b18, J7.b18, J8.b18
/A20: J1.b17, J2.b17, J3.b17, J4.b17, J5.b17, J6.b17, J7.b17, J8.b17
/A21: J1.b15, J2.b15, J3.b15, J4.b15, J5.b15, J6.b15, J7.b15, J8.b15
/A22: J1.b14, J2.b14, J3.b14, J4.b14, J5.b14, J6.b14, J7.b14, J8.b14
/A23: J1.b13, J2.b13, J3.b13, J4.b13, J5.b13, J6.b13, J7.b13, J8.b13
/CLK: J1.c15, J2.c15, J3.c15, J4.c15, J5.c15, J6.c15, J7.c15, J8.c15
/D0: J1.c5, J2.c5, J3.c5, J4.c5, J5.c5, J6.c5, J7.c5, J8.c5
/D1: J1.c4, J2.c4, J3.c4, J4.c4, J5.c4, J6.c4, J7.c4, J8.c4
/D2: J1.c3, J2.c3, J3.c3, J4.c3, J5.c3, J6.c3, J7.c3, J8.c3
/D3: J1.c2, J2.c2, J3.c2, J4.c2, J5.c2, J6.c2, J7.c2, J8.c2
/D4: J1.c1, J2.c1, J3.c1, J4.c1, J5.c1, J6.c1, J7.c1, J8.c1
/D5: J1.b1, J2.b1, J3.b1, J4.b1, J5.b1, J6.b1, J7.b1, J8.b1
/D6: J1.b2, J2.b2, J3.b2, J4.b2, J5.b2, J6.b2, J7.b2, J8.b2
/D7: J1.b3, J2.b3, J3.b3, J4.b3, J5.b3, J6.b3, J7.b3, J8.b3
/D8: J1.b4, J2.b4, J3.b4, J4.b4, J5.b4, J6.b4, J7.b4, J8.b4
/D9: J1.b5, J2.b5, J3.b5, J4.b5, J5.b5, J6.b5, J7.b5, J8.b5
/D10: J1.b6, J2.b6, J3.b6, J4.b6, J5.b6, J6.b6, J7.b6, J8.b6
/D11: J1.b7, J2.b7, J3.b7, J4.b7, J5.b7, J6.b7, J7.b7, J8.b7
/D12: J1.b8, J2.b8, J3.b8, J4.b8, J5.b8, J6.b8, J7.b8, J8.b8
/D13: J1.b9, J2.b9, J3.b9, J4.b9, J5.b9, J6.b9, J7.b9, J8.b9
/D14: J1.b10, J2.b10, J3.b10, J4.b10, J5.b10, J6.b10, J7.b10, J8.b10
/D15: J1.b11, J2.b11, J3.b11, J4.b11, J5.b11, J6.b11, J7.b11, J8.b11
/E: J1.c20, J2.c20, J3.c20, J4.c20, J5.c20, J6.c20, J7.c20, J8.c20
/FC0: J1.c28, J2.c28, J3.c28, J4.c28, J5.c28, J6.c28, J7.c28, J8.c28
/FC1: J1.c27, J2.c27, J3.c27, J4.c27, J5.c27, J6.c27, J7.c27, J8.c27
/FC2: J1.c26, J2.c26, J3.c26, J4.c26, J5.c26, J6.c26, J7.c26, J8.c26
/R/~W: J1.c9, J2.c9, J3.c9, J4.c9, J5.c9, J6.c9, J7.c9, J8.c9
/TMP0: J1.a4, J2.a4, J3.a4, J4.a4, J5.a4, J6.a4, J7.a4, J8.a4
/TMP1: J1.a5, J2.a5, J3.a5, J4.a5, J5.a5, J6.a5, J7.a5, J8.a5
/TMP2: J1.a7, J2.a7, J3.a7, J4.a7, J5.a7, J6.a7, J7.a7, J8.a7
/TMP3: J1.a8, J2.a8, J3.a8, J4.a8, J5.a8, J6.a8, J7.a8, J8.a8
/TMP4: J1.a10, J2.a10, J3.a10, J4.a10, J5.a10, J6.a10, J7.a10, J8.a10
/TMP5: J1.a11, J2.a11, J3.a11, J4.a11, J5.a11, J6.a11, J7.a11, J8.a11
/TMP10: J1.a19, J2.a19, J3.a19, J4.a19, J5.a19, J6.a19, J7.a19, J8.a19
/TMP11: J1.a20, J2.a20, J3.a20, J4.a20, J5.a20, J6.a20, J7.a20, J8.a20
/TMP12: J1.a22, J2.a22, J3.a22, J4.a22, J5.a22, J6.a22, J7.a22, J8.a22
/TMP13: J1.a23, J2.a23, J3.a23, J4.a23, J5.a23, J6.a23, J7.a23, J8.a23
/TMP14: J1.a25, J2.a25, J3.a25, J4.a25, J5.a25, J6.a25, J7.a25, J8.a25
/TMP15: J1.a26, J2.a26, J3.a26, J4.a26, J5.a26, J6.a26, J7.a26, J8.a26
/TMP16: J1.a28, J2.a28, J3.a28, J4.a28, J5.a28, J6.a28, J7.a28, J8.a28
/TMP17: J1.a29, J2.a29, J3.a29, J4.a29, J5.a29, J6.a29, J7.a29, J8.a29
/TMP18: J1.a31, J2.a31, J3.a31, J4.a31, J5.a31, J6.a31, J7.a31, J8.a31
/TMP19: J1.a32, J2.a32, J3.a32, J4.a32, J5.a32, J6.a32, J7.a32, J8.a32
/~A20: J1.a17, J2.a17, J3.a17, J4.a17, J5.a17, J6.a17, J7.a17, J8.a17
/~A21: J1.a16, J2.a16, J3.a16, J4.a16, J5.a16, J6.a16, J7.a16, J8.a16
/~A22: J1.a14, J2.a14, J3.a14, J4.a14, J5.a14, J6.a14, J7.a14, J8.a14
/~A23: J1.a13, J2.a13, J3.a13, J4.a13, J5.a13, J6.a13, J7.a13, J8.a13
/~AS: J1.c6, J2.c6, J3.c6, J4.c6, J5.c6, J6.c6, J7.c6, J8.c6
/~BERR: J1.c22, J2.c22, J3.c22, J4.c22, J5.c22, J6.c22, J7.c22, J8.c22
/~BG: J1.c11, J2.c11, J3.c11, J4.c11, J5.c11, J6.c11, J7.c11, J8.c11
/~BGACK: J1.c12, J2.c12, J3.c12, J4.c12, J5.c12, J6.c12, J7.c12, J8.c12
/~BR: J1.c13, J2.c13, J3.c13, J4.c13, J5.c13, J6.c13, J7.c13, J8.c13
/~DTACK: J1.c10, J2.c10, J3.c10, J4.c10, J5.c10, J6.c10, J7.c10, J8.c10
/~HALT: J1.c17, J2.c17, J3.c17, J4.c17, J5.c17, J6.c17, J7.c17, J8.c17
/~IPL0: J1.c25, J2.c25, J3.c25, J4.c25, J5.c25, J6.c25, J7.c25, J8.c25
/~IPL1: J1.c24, J2.c24, J3.c24, J4.c24, J5.c24, J6.c24, J7.c24, J8.c24
/~IPL2: J1.c23, J2.c23, J3.c23, J4.c23, J5.c23, J6.c23, J7.c23, J8.c23
/~LDS: J1.c8, J2.c8, J3.c8, J4.c8, J5.c8, J6.c8, J7.c8, J8.c8
/~RD_L: J1.b16, J2.b16, J3.b16, J4.b16, J5.b16, J6.b16, J7.b16, J8.b16
/~RD_U: J1.c16, J2.c16, J3.c16, J4.c16, J5.c16, J6.c16, J7.c16, J8.c16
/~RST: J1.c18, J2.c18, J3.c18, J4.c18, J5.c18, J6.c18, J7.c18, J8.c18, J10.5
/~UDS: J1.c7, J2.c7, J3.c7, J4.c7, J5.c7, J6.c7, J7.c7, J8.c7
/~VMA: J1.c19, J2.c19, J3.c19, J4.c19, J5.c19, J6.c19, J7.c19, J8.c19
/~VPA: J1.c21, J2.c21, J3.c21, J4.c21, J5.c21, J6.c21, J7.c21, J8.c21
/~WR_L: J1.b12, J2.b12, J3.b12, J4.b12, J5.b12, J6.b12, J7.b12, J8.b12
/~WR_U: J1.c14, J2.c14, J3.c14, J4.c14, J5.c14, J6.c14, J7.c14, J8.c14
GND: C1.2, C2.2, C3.2, C4.2, C5.2, C6.2, C7.2, C8.2, C9.2, D1.2 (A), J1.a3, J1.a6, J1.a9, J1.a12, J1.a15, J1.a18, J1.a21, J1.a24, J1.a27, J1.a30, J2.a3, J2.a6, J2.a9, J2.a12, J2.a15, J2.a18, J2.a21, J2.a24, J2.a27, J2.a30, J3.a3, J3.a6, J3.a9, J3.a12, J3.a15, J3.a18, J3.a21, J3.a24, J3.a27, J3.a30, J4.a3, J4.a6, J4.a9, J4.a12, J4.a15, J4.a18, J4.a21, J4.a24, J4.a27, J4.a30, J5.a3, J5.a6, J5.a9, J5.a12, J5.a15, J5.a18, J5.a21, J5.a24, J5.a27, J5.a30, J6.a3, J6.a6, J6.a9, J6.a12, J6.a15, J6.a18, J6.a21, J6.a24, J6.a27, J6.a30, J7.a3, J7.a6, J7.a9, J7.a12, J7.a15, J7.a18, J7.a21, J7.a24, J7.a27, J7.a30, J8.a3, J8.a6, J8.a9, J8.a12, J8.a15, J8.a18, J8.a21, J8.a24, J8.a27, J8.a30, J9.2, J10.4, U1.2 (GND)
PWR_LED: J10.3, R1.1
PWR_SWT_0: J9.1, J10.1
PWR_SWT_1: C8.1, D2.1 (K), J10.2, U1.1 (IN)
